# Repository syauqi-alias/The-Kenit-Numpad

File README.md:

# The-Kenit-Numpad
The design and logo is copyright right fully owned by Syauqi Alias.

A custom numpad with THT component. Experiment with KiCad 6 round track plugin.

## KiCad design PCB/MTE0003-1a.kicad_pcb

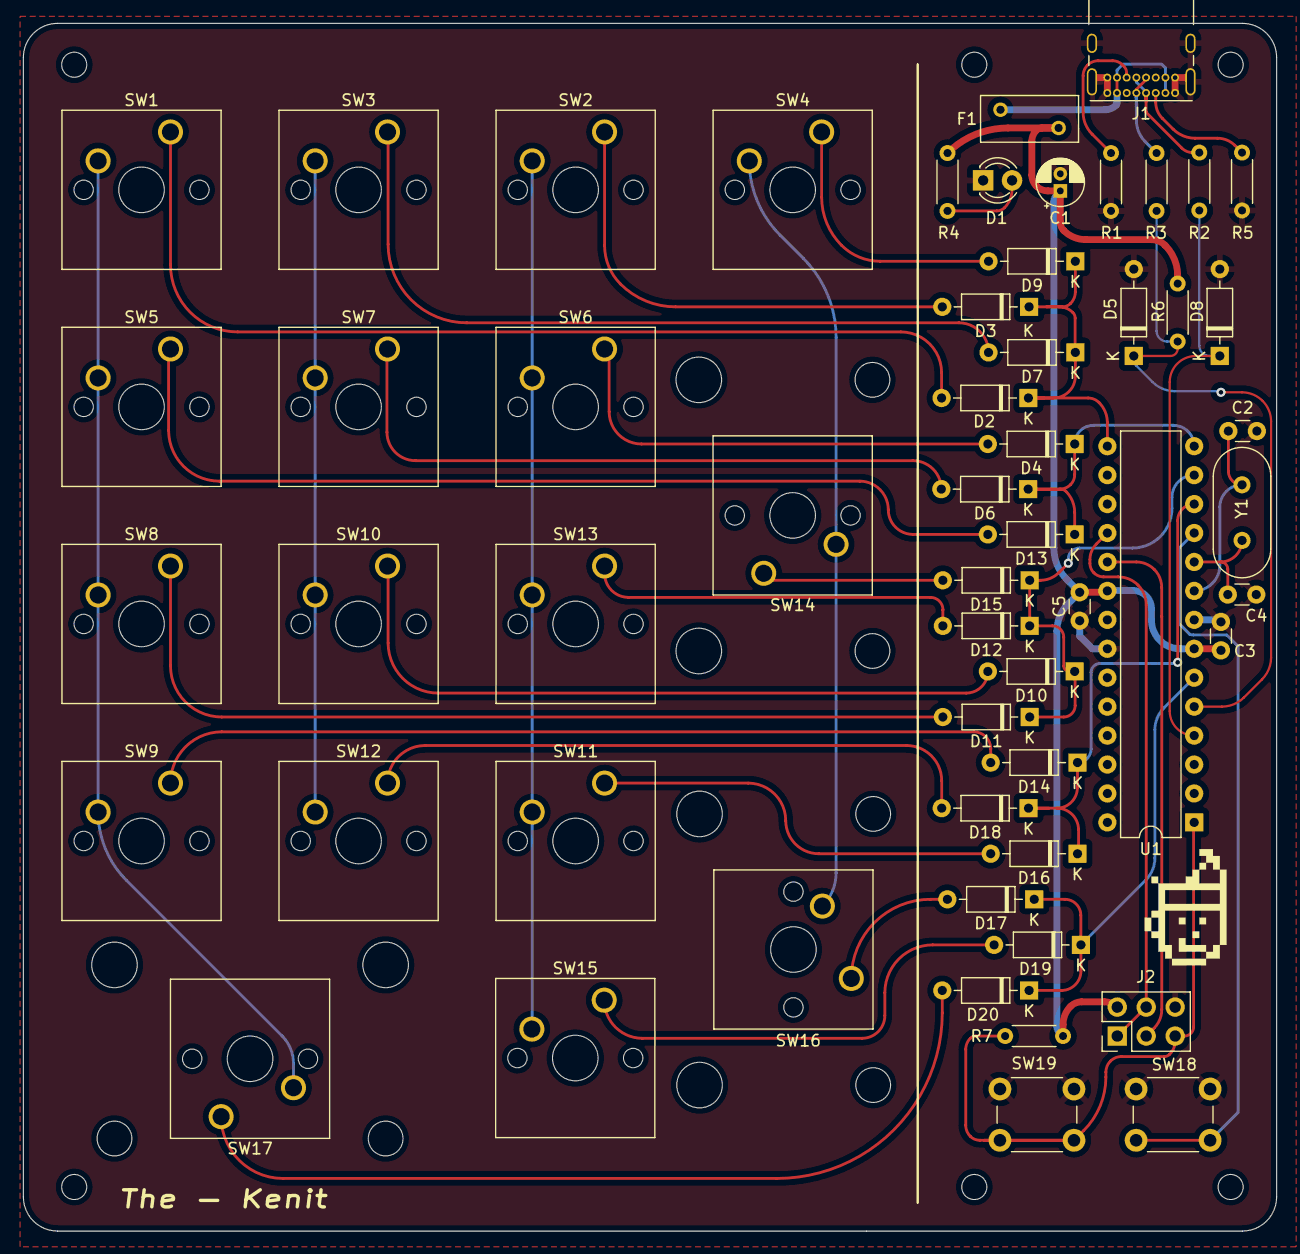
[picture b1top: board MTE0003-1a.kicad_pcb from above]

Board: 2 copper layers, 110.0 x 106.0 mm, 56 parts (0 on the bottom side), 42 nets.

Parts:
C1: 4.7uF; CP_Radial_D4.0mm_P1.50mm
C2, C4: 22pF; C_Disc_D3.0mm_W1.6mm_P2.50mm
C3, C5: 0.1uF; C_Disc_D3.0mm_W1.6mm_P2.50mm
D1: LED; LED_D3.0mm
D2, D3, D4, D6, D7, D9, D10, D11, D12, D13, D14, D15, D16, D17, D18, D19, D20: D; D_DO-35_SOD27_P7.62mm_Horizontal
D5, D8: 3.6V; D_DO-35_SOD27_P7.62mm_Horizontal
F1: 500mA; Fuse_BelFuse_0ZRE0005FF_L8.3mm_W3.8mm
J1: USB_C_Receptacle_USB2.0; USB_C_Receptacle_GCT_USB4085
J2: AVR-ISP-6; PinHeader_2x03_P2.54mm_Vertical
R1, R5: 5.1K; R_Axial_DIN0204_L3.6mm_D1.6mm_P5.08mm_Horizontal
R2, R3: 75R; R_Axial_DIN0204_L3.6mm_D1.6mm_P5.08mm_Horizontal
R4, R6: 1.5K; R_Axial_DIN0204_L3.6mm_D1.6mm_P5.08mm_Horizontal
R7: 10K; R_Axial_DIN0204_L3.6mm_D1.6mm_P5.08mm_Horizontal
SW1, SW2, SW3, SW4, SW5, SW6, SW7, SW8, SW9, SW10, SW11, SW12, SW13, SW15: SW_SPST; SW_Cherry_MX_1.00u_PCB
SW14: SW_SPST; SW_Cherry_MX_2.00u_Vertical_PCB
SW16, SW17: SW_SPST; SW_Cherry_MX_2.00u_PCB
SW18: BOOT; SW_PUSH_6mm
SW19: RESET; SW_PUSH_6mm
U1: ATmega328-P; DIP-28_W7.62mm
Y1: Crystal; Crystal_HC49-4H_Vertical

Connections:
+5V: C1.1, C3.1, C5.1, F1.1, J2.2 (VCC), R4.1, R6.2, R7.1, U1.7 (VCC), U1.20 (AVCC)
BOOT: SW18.2 (D), U1.11 (PD5)
D+: D8.1 (K), R2.2, U1.4 (PD2)
D-: D5.1 (K), R3.2, R6.1, U1.5 (PD3)
GND: C1.2, C2.2, C3.2, C4.2, C5.2, D1.1 (K), D5.2 (A), D8.2 (A), J1.A1 (GND), J1.A12 (GND), J1.B1 (GND), J1.B12 (GND), J1.S1 (SHIELD), J2.6 (GND), R1.2, R5.2, SW18.1 (C), SW19.1 (C), U1.8 (GND), U1.22 (GND)
MISO: J2.1 (MISO), J2.4 (MOSI), U1.18 (PB4)
unnamed: D2.2 (A), SW1.1 (A)
unnamed: D7.2 (A), SW3.1 (A)
unnamed: D3.2 (A), SW2.1 (A)
unnamed: D9.2 (A), SW4.1 (A)
unnamed: D13.2 (A), SW5.1 (A)
unnamed: D6.2 (A), SW7.1 (A)
unnamed: D4.2 (A), SW6.1 (A)
unnamed: D11.2 (A), SW8.1 (A)
unnamed: D10.2 (A), SW10.1 (A)
unnamed: D12.2 (A), SW13.1 (A)
unnamed: D15.2 (A), SW14.1 (A)
unnamed: D14.2 (A), SW9.1 (A)
unnamed: D18.2 (A), SW12.1 (A)
unnamed: D16.2 (A), SW11.1 (A)
unnamed: D20.2 (A), SW17.1 (A)
unnamed: D19.2 (A), SW15.1 (A)
unnamed: D17.2 (A), SW16.1 (A)
unnamed: D1.2 (A), R4.2
unnamed: F1.2, J1.A4 (VBUS), J1.A9 (VBUS), J1.B4 (VBUS), J1.B9 (VBUS)
unnamed: J1.A5 (CC1), R5.1
unnamed: J1.A6 (D+), J1.B6 (D+), R2.1
unnamed: J1.A7 (D-), J1.B7 (D-), R3.1
unnamed: J1.B5 (CC2), R1.1
unnamed: SW1.2 (B), SW5.2 (B), SW8.2 (B), SW9.2 (B), SW17.2 (B)
unnamed: SW2.2 (B), SW6.2 (B), SW11.2 (B), SW13.2 (B), SW15.2 (B)
unnamed: SW4.2 (B), SW14.2 (B), SW16.2 (B)
unnamed: SW3.2 (B), SW7.2 (B), SW10.2 (B), SW12.2 (B)
RESET: J2.5 (~RST), R7.2, SW19.2 (D), U1.1 (~RESET/PC6)
ROW0: D2.1 (K), D3.1 (K), D7.1 (K), D9.1 (K), U1.15 (PB1)
ROW1: D4.1 (K), D6.1 (K), D13.1 (K), U1.14 (PB0)
ROW2: D10.1 (K), D11.1 (K), D12.1 (K), D15.1 (K), U1.13 (PD7)
ROW3: D14.1 (K), D16.1 (K), D18.1 (K), U1.12 (PD6)
ROW4: D17.1 (K), D19.1 (K), D20.1 (K), U1.6 (PD4)
SCK: J2.3 (SCK), U1.19 (PB5)
XTAL1: C2.1, U1.9 (XTAL1/PB6), Y1.2
XTAL2: C4.1, U1.10 (XTAL2/PB7), Y1.1

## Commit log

2022-11-01 Create Image
